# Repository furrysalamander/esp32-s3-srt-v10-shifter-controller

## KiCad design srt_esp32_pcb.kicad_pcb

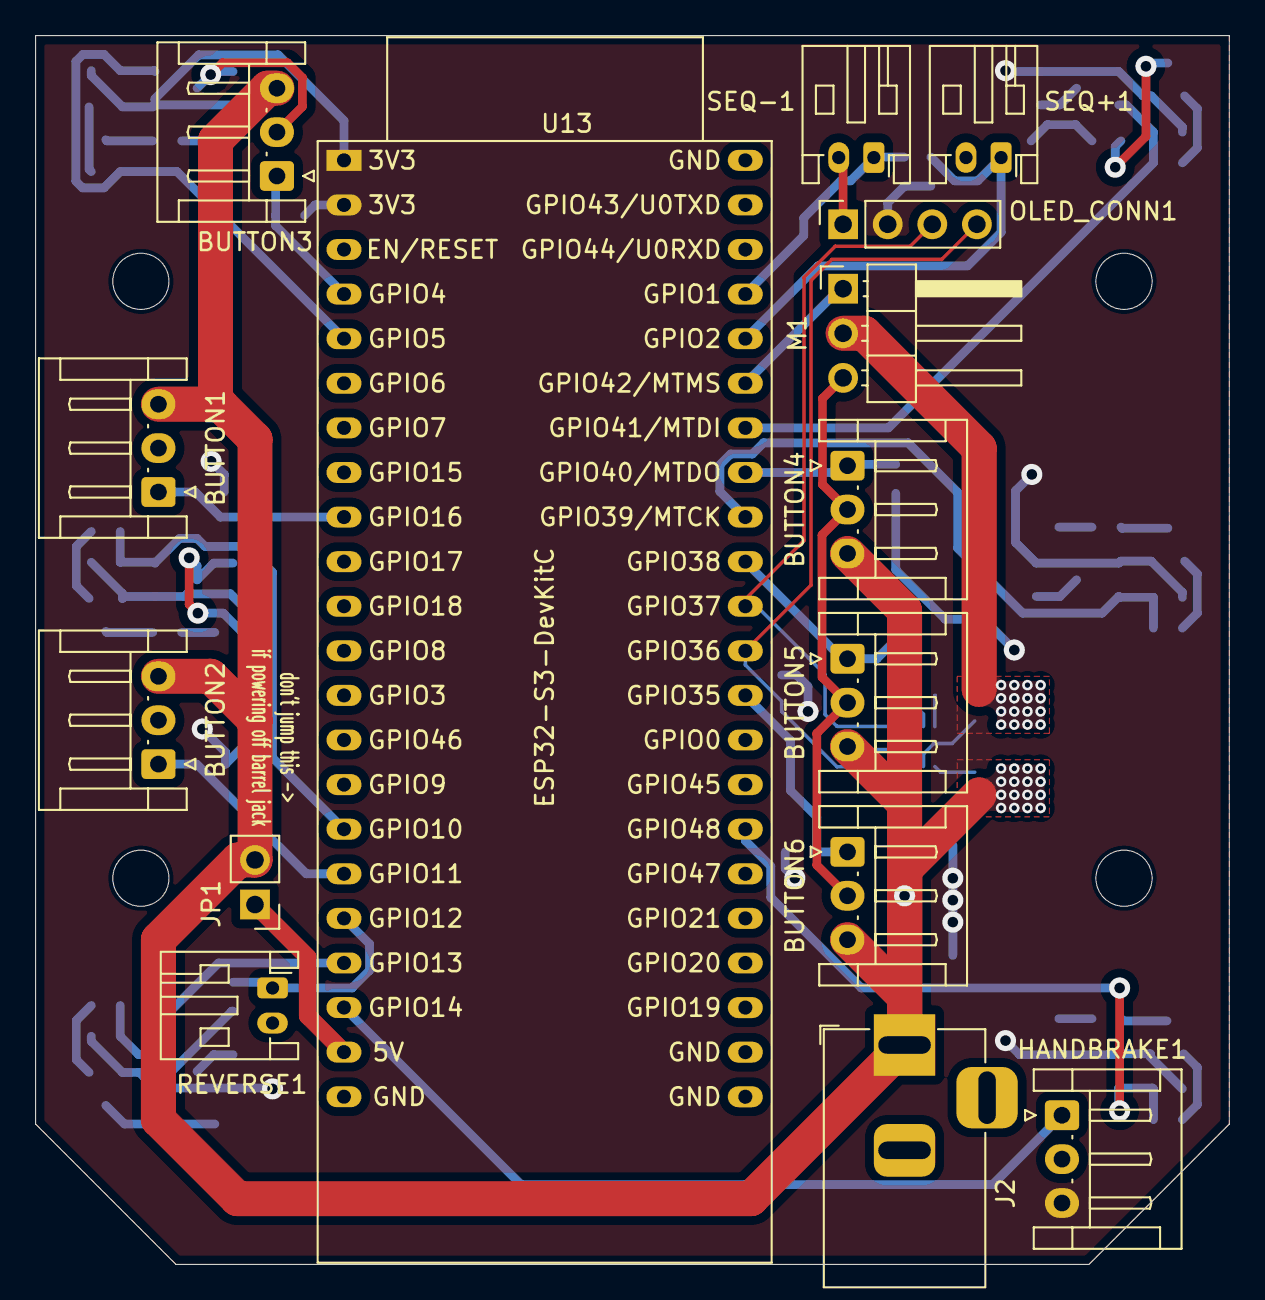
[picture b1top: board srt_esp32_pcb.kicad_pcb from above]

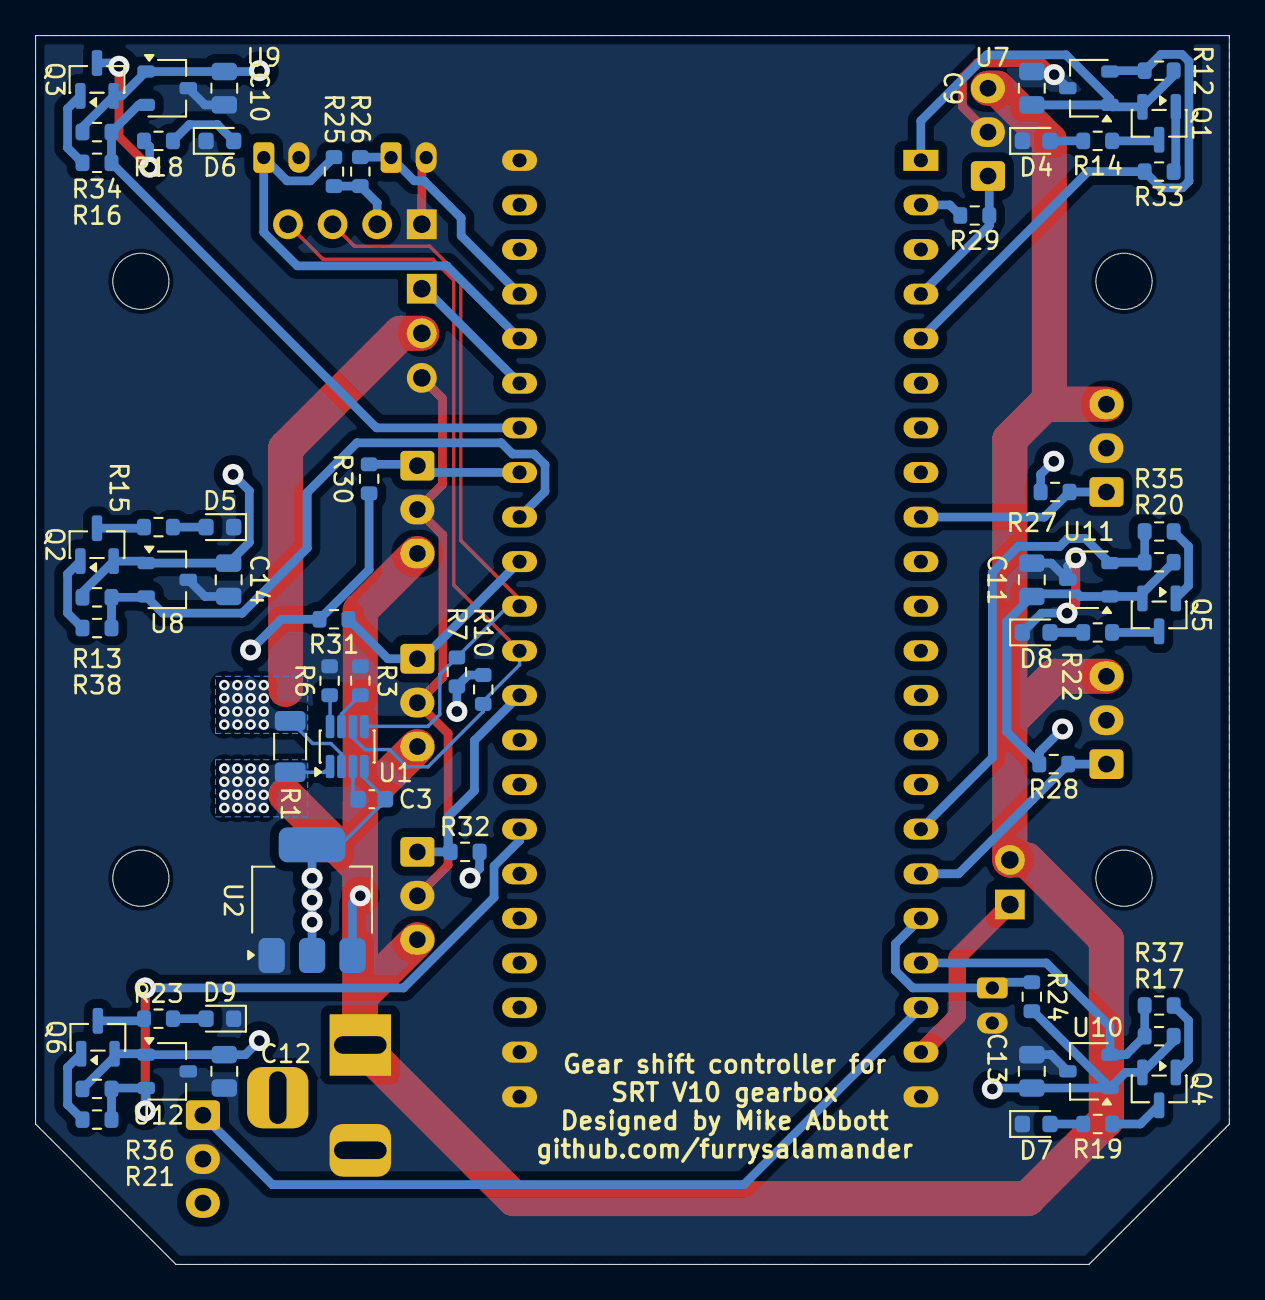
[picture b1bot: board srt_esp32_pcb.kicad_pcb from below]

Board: 2 copper layers, 68.0 x 70.0 mm, 78 parts (59 on the bottom side), 44 nets.

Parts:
BUTTON1, BUTTON2, BUTTON3, BUTTON4, BUTTON5, BUTTON6: Conn_01x03_Socket; JST_EH_S3B-EH_1x03_P2.50mm_Horizontal
C3: 100n; C_0603_1608Metric
C9, C10, C11, C12, C13, C14: 470n; C_0805_2012Metric
D4, D5, D6, D7, D8, D9: LED; LED_0603_1608Metric
H1, H2, H3, H4: MountingHole; MountingHole_3.2mm_M3_DIN965
HANDBRAKE1: Conn_01x03_Socket; JST_EH_S3B-EH_1x03_P2.50mm_Horizontal
J2: Barrel_Jack_Switch; BarrelJack_Horizontal
JP1: POWER_BOARD_OFF_USB; PinHeader_1x02_P2.54mm_Vertical
M1: Motor_Servo; PinHeader_1x03_P2.54mm_Horizontal
OLED_CONN1: Conn_01x04_Socket; PinSocket_1x04_P2.54mm_Vertical
Q1, Q2, Q3, Q4, Q5, Q6: SS8550; SOT-23
R1: 100m; R_1206_3216Metric
R3, R6, R7, R10, R12, R13, R16, R17, R20, R21, R24, R25, R26, R27, R28, R29, R30, R31, R32, R33, R34, R35, R36, R37, R38: 10k; R_0603_1608Metric
R14, R15, R18, R19, R22, R23: 220; R_0603_1608Metric
REVERSE1: Conn_01x02_Socket; JST_PH_S2B-PH-K_1x02_P2.00mm_Horizontal
SEQ+1: Conn_01x02_Socket; JST_PH_S2B-PH-K_1x02_P2.00mm_Horizontal
SEQ-1: Conn_01x02_Socket; JST_PH_S2B-PH-K_1x02_P2.00mm_Horizontal
U1: INA219AxDCN; SOT-23-8
U2: AMS1117-3.3; SOT-223-3_TabPin2
U7, U8, U9, U10, U11, U12: TCS40DLR; SOT-23W
U13: ESP32-S3-DevKitC

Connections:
+3V3: C3.2, C9.2, C10.2, C11.2, C12.2, C13.2, C14.2, HANDBRAKE1.3, OLED_CONN1.2, Q1.2 (E), Q2.2 (E), Q3.2 (E), Q4.2 (E), Q5.2 (E), Q6.2 (E), R7.1, R10.1, R12.2, R13.2, R16.2, R17.2, R20.2, R21.2, R24.2, R25.2, R26.2, R27.2, R28.2, R29.2, R30.2, R31.2, R32.2, U1.4 (VS), U2.2 (VO), U7.1 (V_{CC}), U8.1 (V_{CC}), U9.1 (V_{CC}), U10.1 (V_{CC}), U11.1 (V_{CC}), U12.1 (V_{CC}), U13.1 (3V3), U13.2 (3V3)
+5V: JP1.1 (A), U13.21 (5V)
+6V: BUTTON1.3, BUTTON2.3, BUTTON3.3, BUTTON4.3, BUTTON5.3, BUTTON6.3, J2.1, JP1.2 (B), R1.1, U1.1 (IN+), U2.3 (VI)
+VDC: M1.2 (+), R1.2, U1.2 (IN-)
BUTTON_1: BUTTON1.1, R27.1, U13.9 (GPIO16/ADC2_CH5/32K_N)
BUTTON_2: BUTTON2.1, R28.1, U13.17 (GPIO11/ADC2_CH0)
BUTTON_3: BUTTON3.1, R29.1, U13.4 (GPIO4/ADC1_CH3)
BUTTON_4: BUTTON4.1, R30.1, U13.37 (GPIO40/MTDO)
BUTTON_5: BUTTON5.1, R31.1, U13.35 (GPIO38)
BUTTON_6: BUTTON6.1, R32.1, U13.32 (GPIO35)
GEAR_1: R12.1, R33.2, U7.2 (V_{OUT}), U13.5 (GPIO5/ADC1_CH4)
GEAR_2: R16.1, R34.2, U9.2 (V_{OUT}), U13.38 (GPIO41/MTDI)
GEAR_3: R20.1, R35.2, U11.2 (V_{OUT}), U13.16 (GPIO10/ADC1_CH9)
GEAR_4: R13.1, R38.2, U8.2 (V_{OUT}), U13.36 (GPIO39/MTCK)
GEAR_5: R17.1, R37.2, U10.2 (V_{OUT}), U13.19 (GPIO13/ADC2_CH2)
GEAR_6: R21.1, R36.2, U12.2 (V_{OUT}), U13.29 (GPIO48)
GND: BUTTON1.2, BUTTON2.2, BUTTON3.2, BUTTON4.2, BUTTON5.2, BUTTON6.2, C3.1, C9.1, C10.1, C11.1, C12.1, C13.1, C14.1, D4.1 (K), D5.1 (K), D6.1 (K), D7.1 (K), D8.1 (K), D9.1 (K), HANDBRAKE1.2, J2.2, M1.3 (-), OLED_CONN1.1, R3.2, R6.2, REVERSE1.2, SEQ+1.2, SEQ-1.2, U1.3 (GND), U2.1 (GND), U7.3 (GND), U8.3 (GND), U9.3 (GND), U10.3 (GND), U11.3 (GND), U12.3 (GND), U13.22 (GND), U13.23 (GND), U13.24 (GND), U13.44 (GND)
HANDBRAKE: HANDBRAKE1.1, U13.20 (GPIO14/ADC2_CH3)
I2C_SCL: OLED_CONN1.3, R7.2, U1.5 (SCL), U13.34 (GPIO37)
I2C_SDA: OLED_CONN1.4, R10.2, U1.6 (SDA), U13.33 (GPIO36)
unnamed: D4.2 (A), R14.2
unnamed: D5.2 (A), R15.2
unnamed: D6.2 (A), R18.2
unnamed: D7.2 (A), R19.2
unnamed: D8.2 (A), R22.2
unnamed: D9.2 (A), R23.2
unnamed: Q1.1 (B), R33.1
unnamed: Q1.3 (C), R14.1
unnamed: Q2.1 (B), R38.1
unnamed: Q2.3 (C), R15.1
unnamed: Q3.1 (B), R34.1
unnamed: Q3.3 (C), R18.1
unnamed: Q4.1 (B), R37.1
unnamed: Q4.3 (C), R19.1
unnamed: Q5.1 (B), R35.1
unnamed: Q5.3 (C), R22.1
unnamed: Q6.1 (B), R36.1
unnamed: Q6.3 (C), R23.1
unnamed: R3.1, U1.7 (A0)
unnamed: R6.1, U1.8 (A1)
REVERSE: R24.1, REVERSE1.1, U13.18 (GPIO12/ADC2_CH1)
SEQ_+: R25.1, SEQ+1.1, U13.40 (GPIO2/ADC1_CH1)
SEQ_-: R26.1, SEQ-1.1, U13.41 (GPIO1/ADC1_CH0)
SERVO_PWM: M1.1 (PWM), U13.39 (GPIO42/MTMS)
